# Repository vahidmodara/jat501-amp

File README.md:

# jat501-amp
PCB design for jat501 power amplifier

DOWNLOAD [Click HERE](https://github.com/vahidmodara/jat501-amp/raw/main/jat501-amp.zip)

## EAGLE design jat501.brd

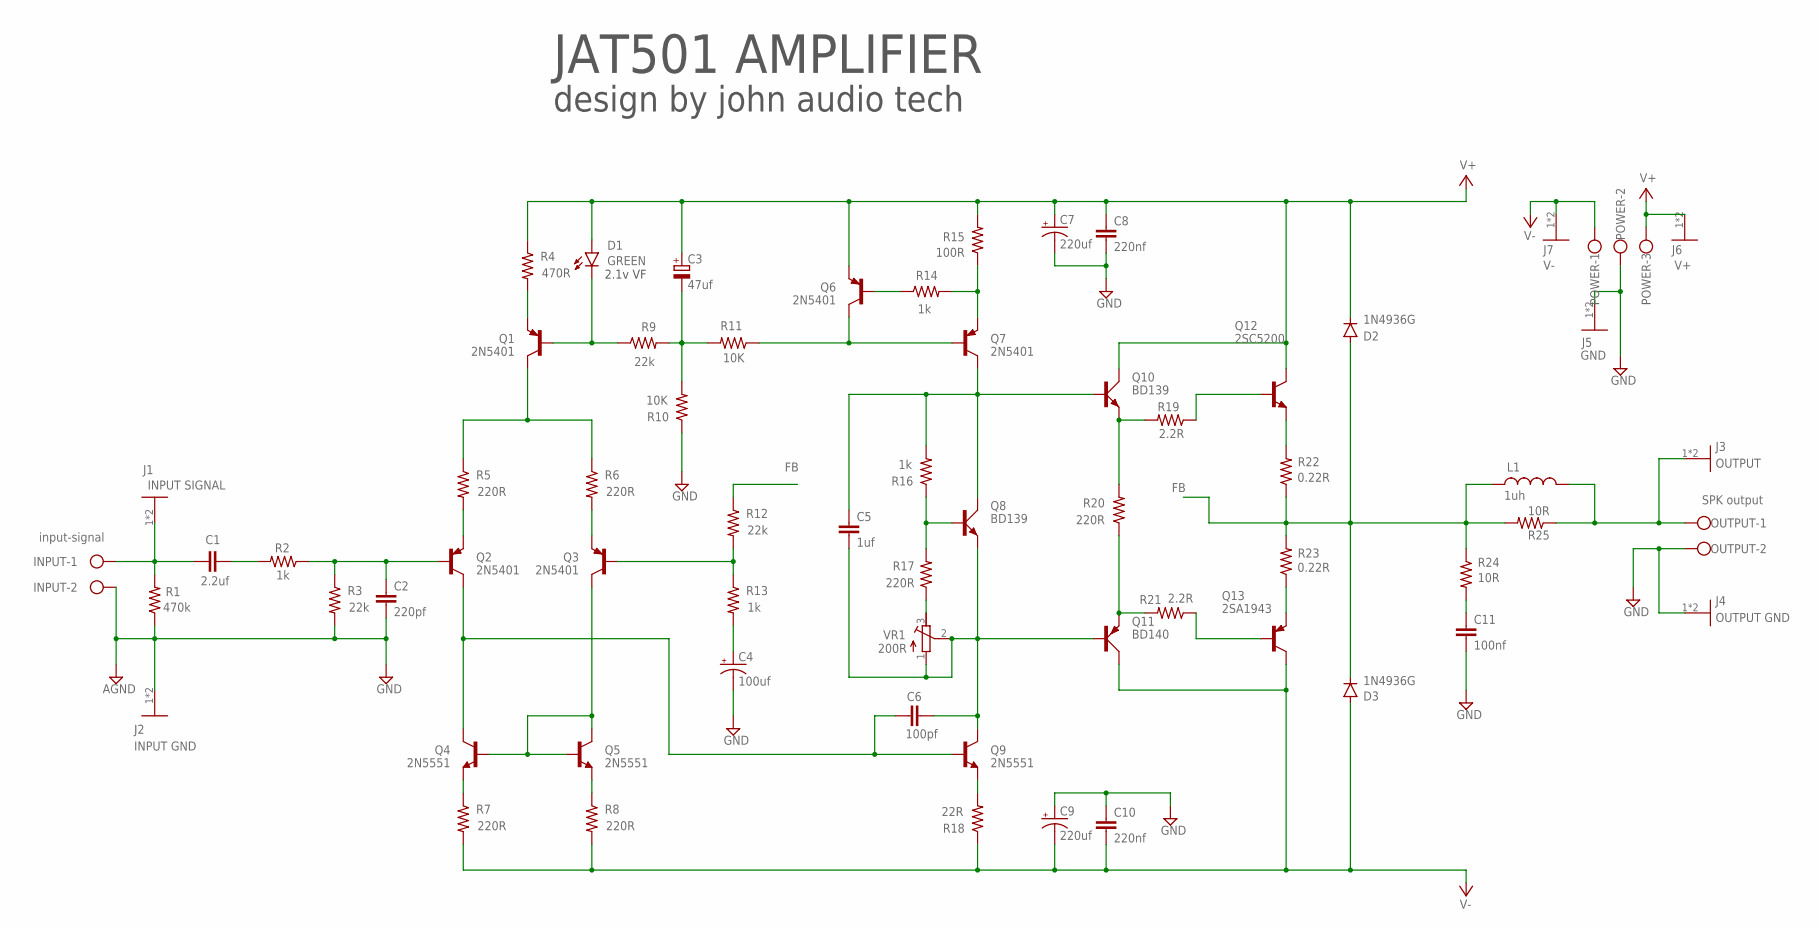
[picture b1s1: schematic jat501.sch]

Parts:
C1: 2.2uf; C150-072X183
C2: 220pf; C050-035X075
C3: 47uf; E5-8,5
C4: 100uf; E5-13
C5: 1uf; C075-063X106
C6: 100pf; C050-035X075
C7, C9: 220uf; E5-13
C8, C10: 220nf; C050-075X075
C11: 100nf; C050-075X075
D1: GREEN; LED_5MM-KIT
D2, D3: 1N4936G; DO41-10
INPUT: input-signal; W237-102
J1: INPUT SIGNAL; TE_1217861-1
J2: INPUT GND; TE_1217861-1
J3: OUTPUT; TE_1217861-1
J4: OUTPUT GND; TE_1217861-1
J5: GND; TE_1217861-1
J6: V+; TE_1217861-1
J7: V-; TE_1217861-1
L1: 1uh; TFI0510
OUTPUT: SPK output; W237-102
POWER: W237-103
Q1, Q2, Q3, Q6, Q7: 2N5401; TO92-EBC
Q4, Q5, Q9: 2N5551; TO92-EBC
Q8, Q10: BD139; TO126AV
Q11: BD140; TO126AV
Q12: 2SC5200; TO-264
Q13: 2SA1943; TO-264
R1: 470k; 0207/10
R2, R13, R14, R16: 1k; 0207/10
R3, R9, R12: 22k; 0207/10
R4: 470R; 0207/10
R5, R6, R7, R8, R17, R20: 220R; 0207/10
R10, R11: 10K; 0207/10
R15: 100R; 0207/10
R18: 22R; 0207/10
R19, R21: 2.2R; 0207/10
R22, R23: 0.22R; 0922/22
R24, R25: 10R; 0922/22
VR1: 200R; RTRIM64W

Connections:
FB: D2.A, D3.C, L1.1, R12.1, R22.1, R23.2, R24.1, R25.2
GND: C2.2, C4.-, C7.-, C8.2, C9.+, C10.1, C11.2, INPUT.2, J2.1, J2.2, J4.1, J4.2, J5.1, J5.2, OUTPUT.2, POWER.2, R1.1, R3.2, R10.1
unnamed: C1.1, INPUT.1, J1.1, J1.2, R1.2
unnamed: C2.1, Q2.B, R2.1, R3.1
unnamed: C1.2, R2.2
unnamed: Q1.C, R5.1, R6.1
unnamed: Q3.E, R6.2
unnamed: Q2.E, R5.2
unnamed: Q10.E, R19.2, R20.2
unnamed: Q3.C, Q4.B, Q5.B, Q5.C
unnamed: Q5.E, R8.1
unnamed: Q4.E, R7.1
unnamed: Q1.E, R4.2
unnamed: C11.1, R24.2
unnamed: D1.K (C), Q1.B, R9.1
unnamed: C3.-, R9.2, R10.2, R11.2
unnamed: Q6.C, Q7.B, R11.1
unnamed: Q3.B, R12.2, R13.1
unnamed: Q6.B, R14.1
unnamed: Q7.E, R14.2, R15.1
unnamed: C4.+, R13.2
unnamed: C5.1, Q7.C, Q8.C, Q10.B, R16.2
unnamed: Q8.B, R16.1, R17.2
unnamed: R17.1, VR1.3 (E)
unnamed: Q9.E, R18.2
unnamed: C5.2, C6.1, Q8.E, Q9.C, Q11.B, VR1.1 (A), VR1.2 (S)
unnamed: C6.2, Q2.C, Q4.C, Q9.B
unnamed: Q11.E, R20.1, R21.2
unnamed: Q12.B, R19.1
unnamed: Q13.B, R21.1
unnamed: Q13.E, R23.1
unnamed: Q12.E, R22.2
OUTPUT: J3.1, J3.2, L1.2, OUTPUT.1, R25.1
V+: C3.+, C7.+, C8.1, D1.A, D2.C, J6.1, J6.2, POWER.3, Q6.E, Q10.C, Q12.C, R4.1, R15.2
V-: C9.-, C10.2, D3.A, J7.1, J7.2, POWER.1, Q11.C, Q13.C, R7.2, R8.2, R18.1

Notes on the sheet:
JAT501 AMPLIFIER
design by john audio tech
2.1v VF

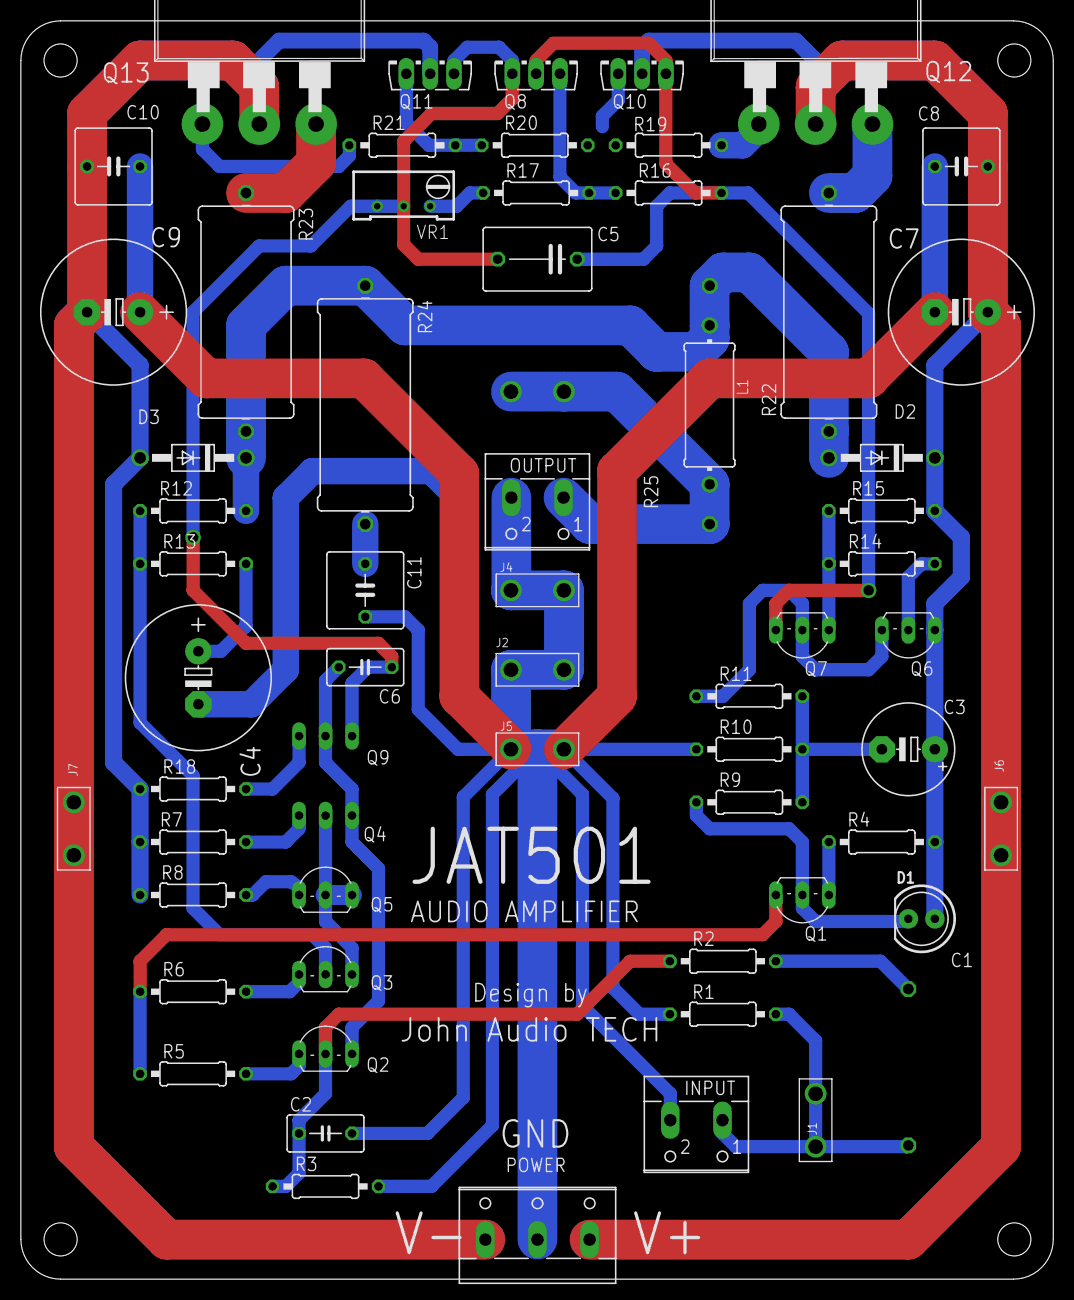
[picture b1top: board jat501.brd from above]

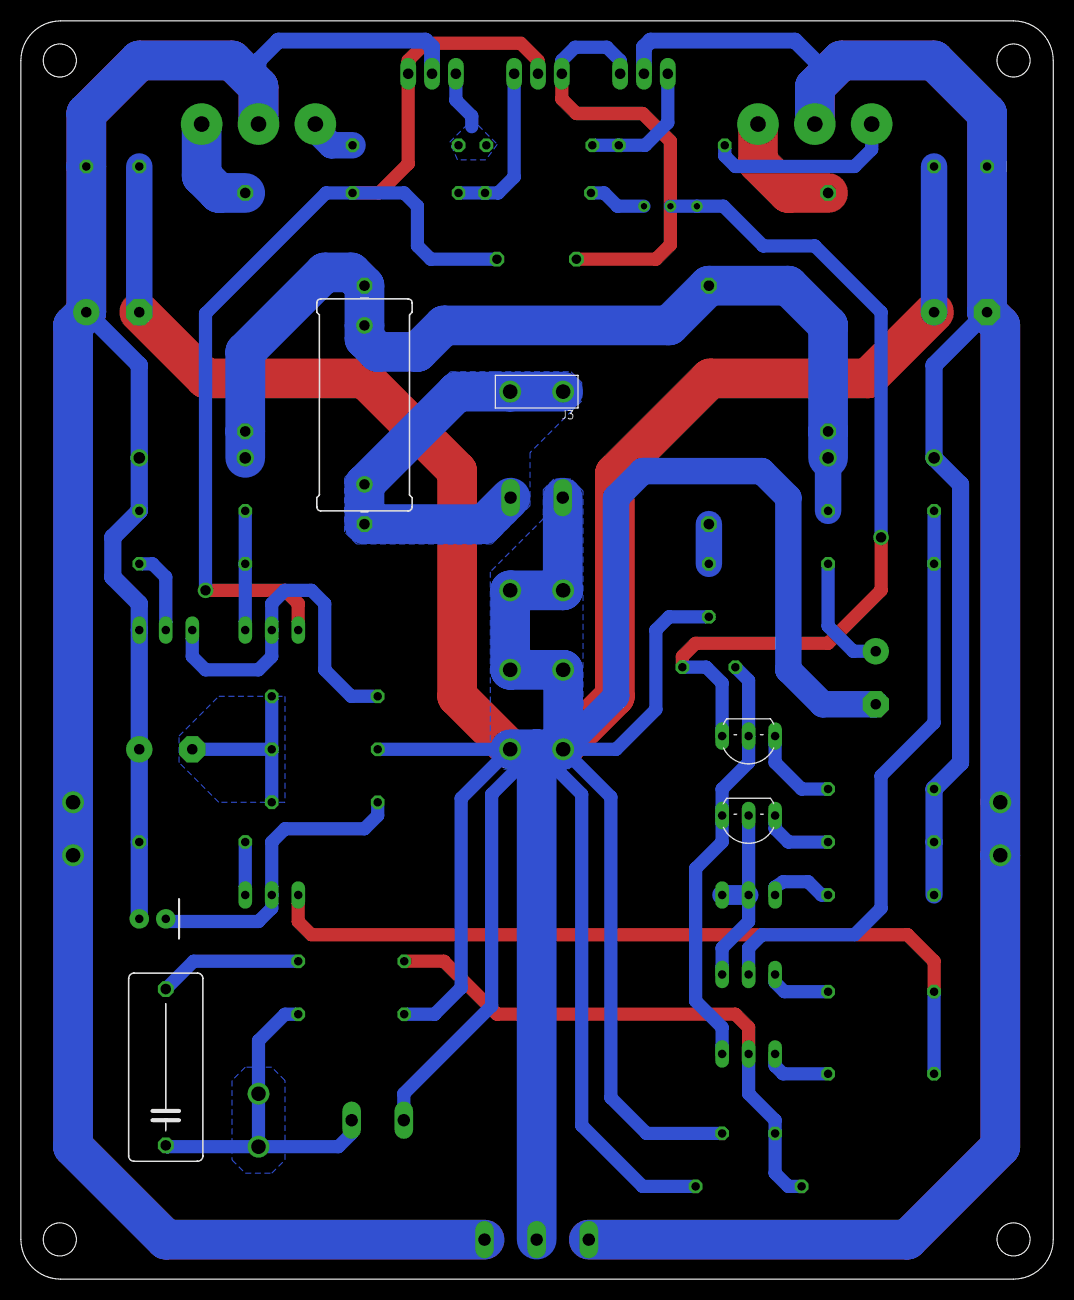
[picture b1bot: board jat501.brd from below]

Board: 2 copper layers, 99.0 x 120.6 mm, 64 parts (5 on the bottom side), 35 nets.

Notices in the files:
parts and their libraries:
SparkFun-LED: Licensing: Creative Commons ShareAlike 4.0 International - https://creativecommons.org/licenses/by-sa/4.0
